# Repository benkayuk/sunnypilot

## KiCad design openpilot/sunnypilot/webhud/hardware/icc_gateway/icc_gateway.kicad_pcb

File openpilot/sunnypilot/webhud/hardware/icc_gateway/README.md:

# ICC CAN gateway board (Fisker Ocean, IBUS1 / IBUS2 man-in-the-middle)

KiCad 10 project. Sits between the car harness and the ICC (head unit) main connector J1
(Molex stAK50h 160013-0641), passes every circuit straight through except the two CAN buses,
which go through a Teensy 4.1 gateway with a normally-closed relay bypass.

## Files

| File | What |
|---|---|
| `icc_gateway.kicad_pro/.kicad_sch` | root sheet: five sub-sheets |
| `connectors.kicad_sch` | J1 (car harness header) and J2 (ICC-side solder field), 58 pass-through nets, CAN taps |
| `power.kicad_sch` | fuse, reverse/TVS protection, LMR36510 5 V buck, wake logic on EN |
| `can.kicad_sch` | 2x TJA1043 (car side, INH wake) + 2x TJA1051T/3 (ICC side), ESD, decoupling |
| `bypass.kicad_sch` | 4x G6S-2 relays (bridge + switched 120 R terminators), ULN2003A driver |
| `mcu.kicad_sch` | Teensy 4.1, MCP2518FD (SPI, 4th CAN), KL15 sense, LEDs, RTC cell |
| `lib/icc_gateway.kicad_sym` | stAK50h connector symbol (2 units: bay A / bay B), typed Teensy 4.1 symbol |
| `lib/icc_gateway.pretty/Molex_stAK50h_160013-0641.kicad_mod` | header footprint built from Molex SD-160013-0001 |
| `lib/icc_gateway.pretty/ICC_wire_pads_2x29.kicad_mod` | J2: 58 solder holes for the ICC pigtail (1.3 mm signal, 2.0 mm power/speaker), grouped like the header |
| `lib/teensy.pretty/Teensy41.kicad_mod` | Teensy 4.1 footprint (XenGi community library) |

Schematic edits were made through the Konnect MCP tools (`tools/konnect_mcp.py` is a stdio client for
it). `tools/design.py` holds the full component and net table, `tools/footprint_stak50h.py` generates
the header footprint, `tools/place_plan.py` the board placement.

## Connector facts (from the Molex sales drawing)

- 2 bays x 29 circuits. Per bay: circuits 1-8 are the 1.20 mm blades (two rows of four on
  4.00 mm pitch, d1.30 holes), circuits 9-29 are 0.50 mm terminals (three rows of seven on
  2.00 mm pitch, d1.10 holes). Rows are 3.00 mm apart at 13.30 / 16.30 / 19.30 / 22.30 / 25.30
  from the locator-peg row; circuits 23-29 are the row nearest the pegs, 1-4 the farthest.
- Locator pegs 2x d3.75 on 29.85 mm centers, 8.85 mm behind the mating-face edge. Bay pitch
  19.60 mm. Body 40.39 mm wide.
- **Pin-1 handedness must be verified on a sample header before ordering boards.** Molex's
  "PCB layout for reference" picture puts circuit 1 bottom-left with the face at the top. The
  section view shows the top face rows landing farthest from the face, and the front view has
  pin 1 top-left, which together put pin 1 on the *right* of a component-side view. The
  footprint therefore mirrors Molex's picture (`MIRROR = True` in `footprint_stak50h.py`).
  Check with a continuity test from the face to the tails on one header; if pin 1 is on the
  left when the face points away from you, set `MIRROR = False` and regenerate.

## Pin assignment (Teensy 4.1)

| Function | Teensy pin |
|---|---|
| CAN1 (car IBUS1, TJA1043 U2) | 22 TX / 23 RX |
| CAN2 (car IBUS2, TJA1043 U3) | 1 TX / 0 RX |
| CAN3 (ICC IBUS1, TJA1051T/3 U4) | 31 TX / 30 RX |
| SPI to MCP2518FD (ICC IBUS2, U5) | 11 MOSI, 12 MISO, 13 SCK, 10 CS, 9 INT |
| Relays RLY1..RLY4 (K1 bridge IBUS1, K2 bridge IBUS2, K3 terms IBUS1, K4 terms IBUS2) | 2, 3, 4, 5 |
| U2 STBN / EN / ERRN | 6 / 7 / 8 |
| U3 STBN / EN / ERRN | 14 / 15 / 16 |
| KL15 sense (100k/22k divider) | 17 (A3) |
| LEDs active / car / ICC | 24 / 25 / 26 |

The Teensy plugs into two 1x24 female 2.54 mm socket strips (add them to the order; they are not
in the schematic BOM). Only the two outer pin rows are used; the inboard VBAT pad cannot reach a
socket, so there is no RTC backup cell.

Cut the Teensy's VUSB-to-VIN pad before the first external power-up.

## ICC side

J2 is a solder field, not a second header. Make one pigtail: a 160014-0014 (bay A, key 4) and a
160014-0011 (bay B, key 1) receptacle with crimped leads, or a salvaged ICC harness stub, and solder the
58 wires into J2 (square pad = circuit 1 of each bay, bay B on the left, bay A on the right, circuits
1-8 on the large holes). This avoids a second header and a second set of 0.5 mm crimps.

## Power and wake

VBATT (J1-A1) -> 0.5 A polyfuse -> SS36 -> SMBJ33A clamp -> `VIN_PROT` -> LMR36510 (5 V, up to
65 V in) -> Teensy VIN. The regulator EN is pulled down and driven through BAT54 diodes from the
two TJA1043 INH outputs and from KL15 (10k), so the board is unpowered while the car sleeps and
wakes on either bus or on ignition. KL15 also feeds both TJA1043 WAKE pins through 10k.

## Relay bypass

De-energized (board off or dead): K1/K2 bridge car<->ICC on both buses and K3/K4 leave the
on-board 120 R terminators disconnected, so the ICC sits on the stock buses. Energized: the
bridges open, the gateway's four transceivers own the four segments, and the terminators
(car-side and ICC-side, both buses) are switched in. Populate R20/R22 (car-side terminators)
only if the measurement at the ICC connector shows the car bus lost its terminator when the
ICC was cut.

## Status (2026-10-07)

- Schematic complete, ERC clean (0/0). `icc_gateway_schematic.pdf`, `icc_gateway_bom.csv`.
- PCB routed and **DRC clean (0 errors)**: 110 x 100 mm, 4 layers (F.Cu signal, In1.Cu GND plane, In2.Cu
  signal, B.Cu signal), solid GND pours top and bottom, netclasses Power 1.0 mm / Audio 0.8 / CAN 0.3 /
  Default 0.15, min clearance 0.15, min track 0.09 (Freerouting neck-downs at pads), vias 0.6/0.3.
  Fab as a JLCPCB 4-layer board. Gerbers + drills: `gerbers/`, `icc_gateway_gerbers.zip`.
  Renders: `routing/icc_gateway_final_top.png`, `routing/icc_gateway_final_bottom.png`.
- Assembly: `assembly/icc_gateway-cpl.csv` (JLCPCB pick-and-place columns, KiCad coordinates, all 66 placed
  footprints on Top, rotations as placed) and `assembly/icc_gateway-bom-jlc.csv` (JLC columns; the LCSC
  part number column is empty and must be filled before ordering SMT assembly). The raw KiCad position
  file is `assembly/icc_gateway-positions.csv`. `assembly/icc_gateway-bom-mouser.csv` is the ordering BOM with
  manufacturer and Mouser part numbers (stock checked 2026-10-07); the MCP2518FD SOIC is backordered at
  Mouser, the MCP2517FD-H/SL is the in-stock drop-in.
- Remaining DRC warnings are cosmetic (silk overlaps, tiny Teensy silk text, the J1 silk box clipped
  at the board edge where the connector face overhangs, four mounting holes not in the schematic).
- Routing was done with Freerouting 2.5.0 (`tools/route_pipeline_r2.sh`: KiCad python DSN export, Freerouting,
  SES import) plus hand fixes in `tools/fixup*.py` and `tools/gnd_fixup.py`.

## Before ordering

1. Verify stAK50h pin-1 handedness on a sample header (see "Connector facts"); flip `MIRROR` and regenerate
   `Molex_stAK50h_160013-0641` + re-run the schematic sync if it is wrong.
2. Check J1's mating-face overhang against the enclosure: the face sits 8.85 mm in front of the pegs and
   the board edge is at the face plane.
3. Measure the car-side bus termination before populating R20/R22.

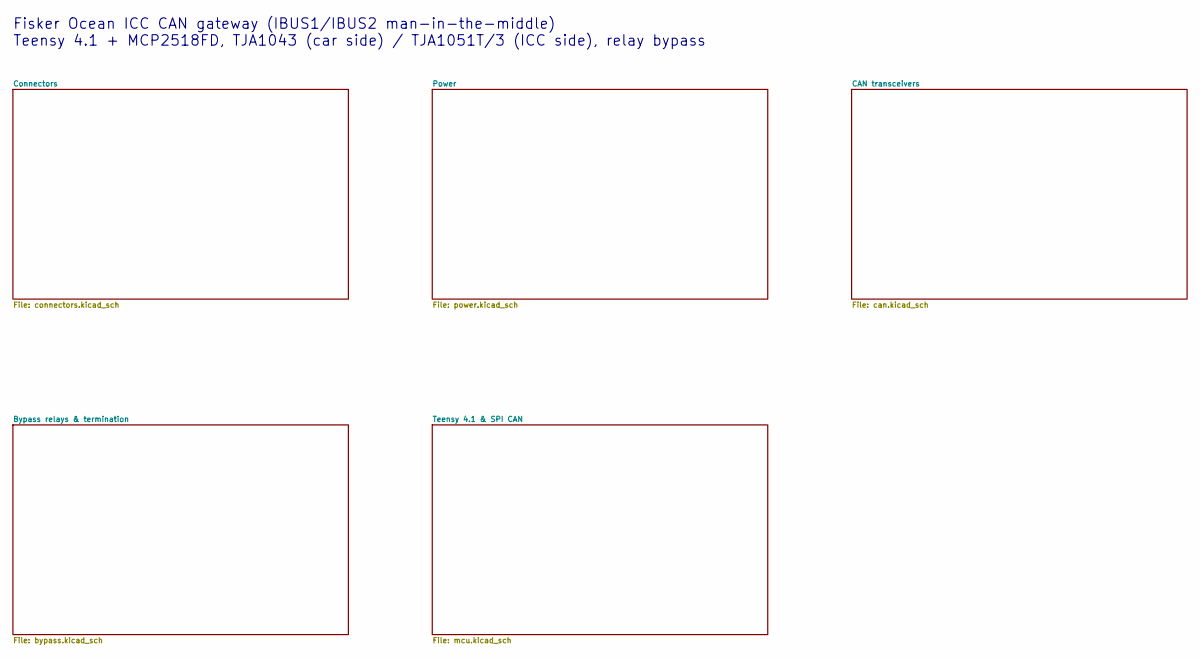
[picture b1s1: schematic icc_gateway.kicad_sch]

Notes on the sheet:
Fisker Ocean ICC CAN gateway (IBUS1/IBUS2 man-in-the-middle) Teensy 4.1 + MCP2518FD, TJA1043 (car side) / TJA1051T/3 (ICC side), relay bypass

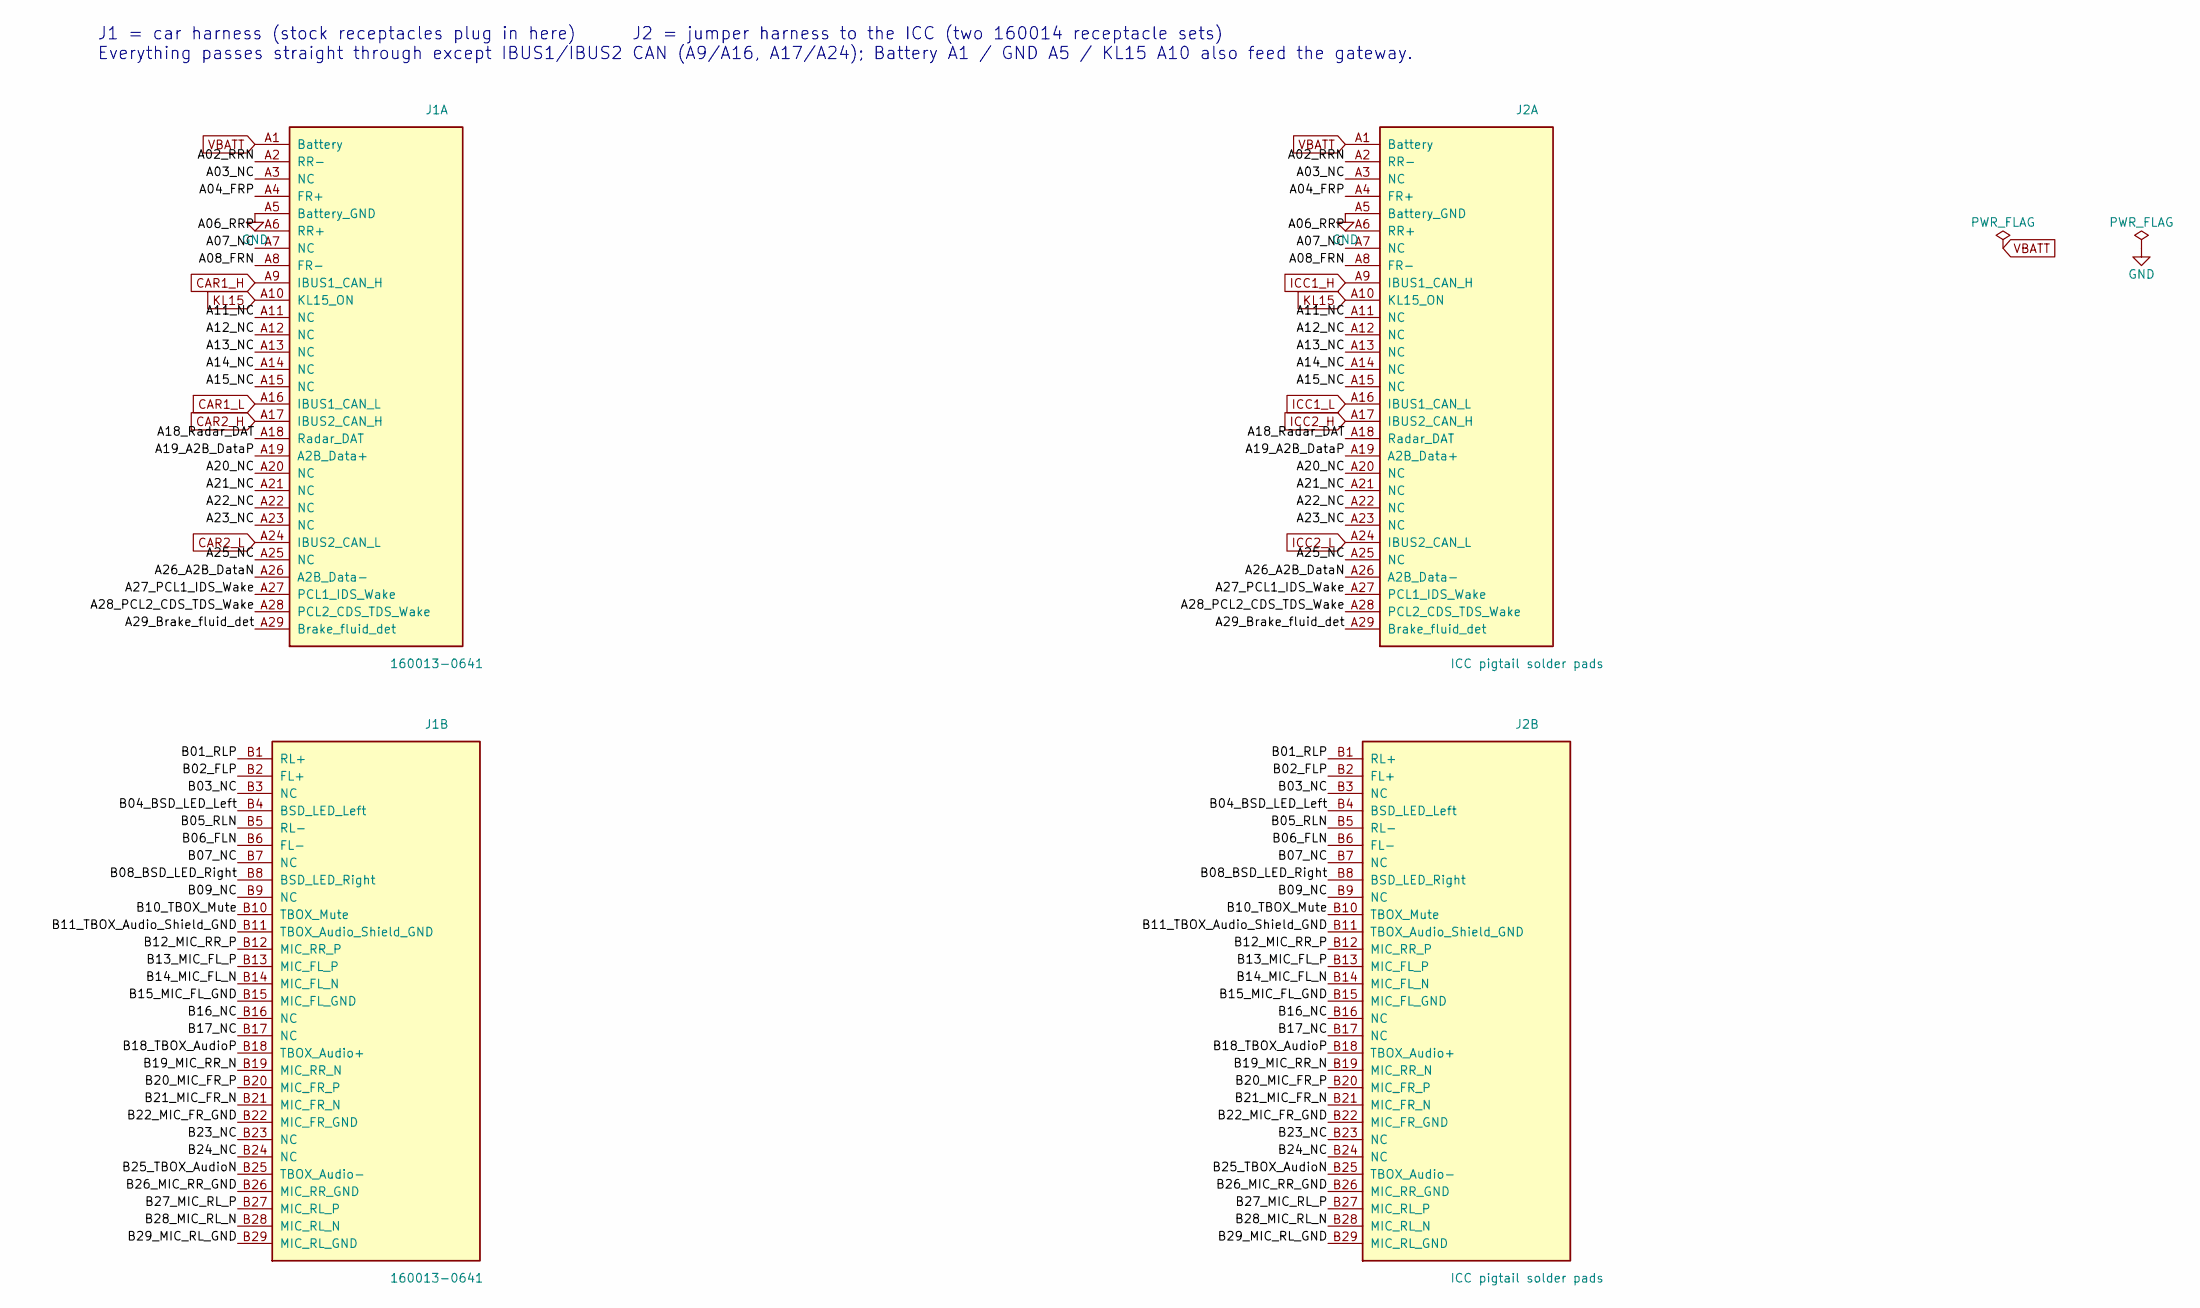
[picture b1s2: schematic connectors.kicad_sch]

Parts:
J1: 160013-0641; Molex_stAK50h_160013-0641
J2: ICC pigtail solder pads; ICC_wire_pads_2x29

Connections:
/Connectors/A02_RRN: J1.A2 (RR-), J2.A2 (RR-)
/Connectors/A03_NC: J1.A3 (NC), J2.A3 (NC)
/Connectors/A04_FRP: J1.A4 (FR+), J2.A4 (FR+)
/Connectors/A06_RRP: J1.A6 (RR+), J2.A6 (RR+)
/Connectors/A07_NC: J1.A7 (NC), J2.A7 (NC)
/Connectors/A08_FRN: J1.A8 (FR-), J2.A8 (FR-)
/Connectors/A11_NC: J1.A11 (NC), J2.A11 (NC)
/Connectors/A12_NC: J1.A12 (NC), J2.A12 (NC)
/Connectors/A13_NC: J1.A13 (NC), J2.A13 (NC)
/Connectors/A14_NC: J1.A14 (NC), J2.A14 (NC)
/Connectors/A15_NC: J1.A15 (NC), J2.A15 (NC)
/Connectors/A18_Radar_DAT: J1.A18 (Radar_DAT), J2.A18 (Radar_DAT)
/Connectors/A19_A2B_DataP: J1.A19 (A2B_Data+), J2.A19 (A2B_Data+)
/Connectors/A20_NC: J1.A20 (NC), J2.A20 (NC)
/Connectors/A21_NC: J1.A21 (NC), J2.A21 (NC)
/Connectors/A22_NC: J1.A22 (NC), J2.A22 (NC)
/Connectors/A23_NC: J1.A23 (NC), J2.A23 (NC)
/Connectors/A25_NC: J1.A25 (NC), J2.A25 (NC)
/Connectors/A26_A2B_DataN: J1.A26 (A2B_Data-), J2.A26 (A2B_Data-)
/Connectors/A27_PCL1_IDS_Wake: J1.A27 (PCL1_IDS_Wake), J2.A27 (PCL1_IDS_Wake)
/Connectors/A28_PCL2_CDS_TDS_Wake: J1.A28 (PCL2_CDS_TDS_Wake), J2.A28 (PCL2_CDS_TDS_Wake)
/Connectors/A29_Brake_fluid_det: J1.A29 (Brake_fluid_det), J2.A29 (Brake_fluid_det)
/Connectors/B01_RLP: J1.B1 (RL+), J2.B1 (RL+)
/Connectors/B02_FLP: J1.B2 (FL+), J2.B2 (FL+)
/Connectors/B03_NC: J1.B3 (NC), J2.B3 (NC)
/Connectors/B04_BSD_LED_Left: J1.B4 (BSD_LED_Left), J2.B4 (BSD_LED_Left)
/Connectors/B05_RLN: J1.B5 (RL-), J2.B5 (RL-)
/Connectors/B06_FLN: J1.B6 (FL-), J2.B6 (FL-)
/Connectors/B07_NC: J1.B7 (NC), J2.B7 (NC)
/Connectors/B08_BSD_LED_Right: J1.B8 (BSD_LED_Right), J2.B8 (BSD_LED_Right)
/Connectors/B09_NC: J1.B9 (NC), J2.B9 (NC)
/Connectors/B10_TBOX_Mute: J1.B10 (TBOX_Mute), J2.B10 (TBOX_Mute)
/Connectors/B11_TBOX_Audio_Shield_GND: J1.B11 (TBOX_Audio_Shield_GND), J2.B11 (TBOX_Audio_Shield_GND)
/Connectors/B12_MIC_RR_P: J1.B12 (MIC_RR_P), J2.B12 (MIC_RR_P)
/Connectors/B13_MIC_FL_P: J1.B13 (MIC_FL_P), J2.B13 (MIC_FL_P)
/Connectors/B14_MIC_FL_N: J1.B14 (MIC_FL_N), J2.B14 (MIC_FL_N)
/Connectors/B15_MIC_FL_GND: J1.B15 (MIC_FL_GND), J2.B15 (MIC_FL_GND)
/Connectors/B16_NC: J1.B16 (NC), J2.B16 (NC)
/Connectors/B17_NC: J1.B17 (NC), J2.B17 (NC)
/Connectors/B18_TBOX_AudioP: J1.B18 (TBOX_Audio+), J2.B18 (TBOX_Audio+)
/Connectors/B19_MIC_RR_N: J1.B19 (MIC_RR_N), J2.B19 (MIC_RR_N)
/Connectors/B20_MIC_FR_P: J1.B20 (MIC_FR_P), J2.B20 (MIC_FR_P)
/Connectors/B21_MIC_FR_N: J1.B21 (MIC_FR_N), J2.B21 (MIC_FR_N)
/Connectors/B22_MIC_FR_GND: J1.B22 (MIC_FR_GND), J2.B22 (MIC_FR_GND)
/Connectors/B23_NC: J1.B23 (NC), J2.B23 (NC)
/Connectors/B24_NC: J1.B24 (NC), J2.B24 (NC)
/Connectors/B25_TBOX_AudioN: J1.B25 (TBOX_Audio-), J2.B25 (TBOX_Audio-)
/Connectors/B26_MIC_RR_GND: J1.B26 (MIC_RR_GND), J2.B26 (MIC_RR_GND)
/Connectors/B27_MIC_RL_P: J1.B27 (MIC_RL_P), J2.B27 (MIC_RL_P)
/Connectors/B28_MIC_RL_N: J1.B28 (MIC_RL_N), J2.B28 (MIC_RL_N)
/Connectors/B29_MIC_RL_GND: J1.B29 (MIC_RL_GND), J2.B29 (MIC_RL_GND)
CAR1_H: J1.A9 (IBUS1_CAN_H); also elsewhere on the board
CAR1_L: J1.A16 (IBUS1_CAN_L); also elsewhere on the board
CAR2_H: J1.A17 (IBUS2_CAN_H); also elsewhere on the board
CAR2_L: J1.A24 (IBUS2_CAN_L); also elsewhere on the board
GND: J1.A5 (Battery_GND), J2.A5 (Battery_GND); also elsewhere on the board
ICC1_H: J2.A9 (IBUS1_CAN_H); also elsewhere on the board
ICC1_L: J2.A16 (IBUS1_CAN_L); also elsewhere on the board
ICC2_H: J2.A17 (IBUS2_CAN_H); also elsewhere on the board
ICC2_L: J2.A24 (IBUS2_CAN_L); also elsewhere on the board
KL15: J1.A10 (KL15_ON), J2.A10 (KL15_ON); also elsewhere on the board
VBATT: J1.A1 (Battery), J2.A1 (Battery); also elsewhere on the board

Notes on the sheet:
J1 = car harness (stock receptacles plug in here) J2 = jumper harness to the ICC (two 160014 receptacle sets) Everything passes straight through except IBUS1/IBUS2 CAN (A9/A16, A17/A24); Battery A1 / GND A5 / KL15 A10 also feed the gateway.

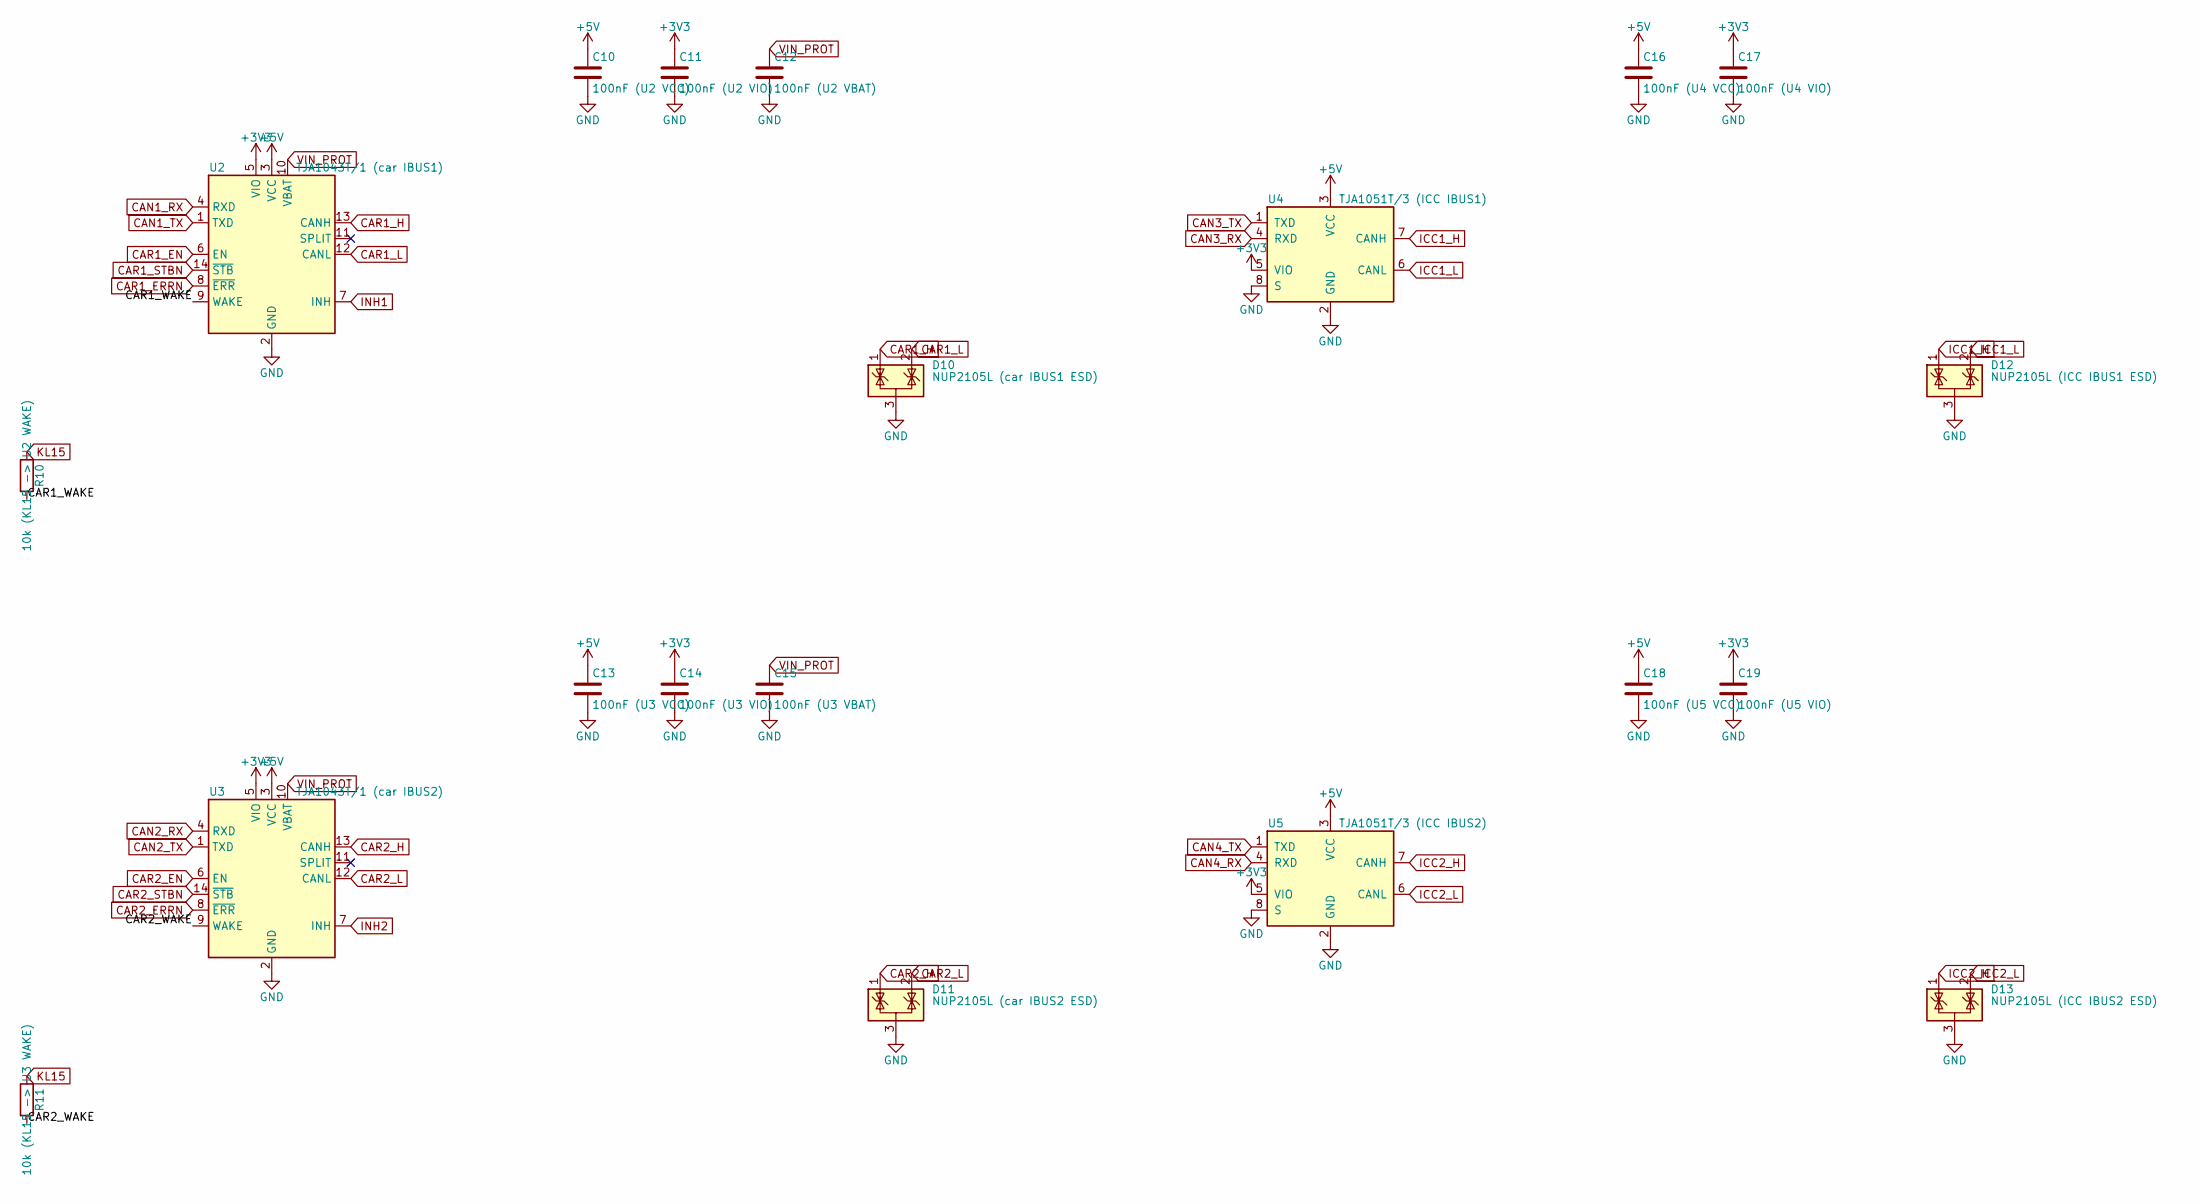
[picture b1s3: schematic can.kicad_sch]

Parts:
C10: 100nF (U2 VCC); C_0805_2012Metric
C11: 100nF (U2 VIO); C_0805_2012Metric
C12: 100nF (U2 VBAT); C_0805_2012Metric
C13: 100nF (U3 VCC); C_0805_2012Metric
C14: 100nF (U3 VIO); C_0805_2012Metric
C15: 100nF (U3 VBAT); C_0805_2012Metric
C16: 100nF (U4 VCC); C_0805_2012Metric
C17: 100nF (U4 VIO); C_0805_2012Metric
C18: 100nF (U5 VCC); C_0805_2012Metric
C19: 100nF (U5 VIO); C_0805_2012Metric
D10: NUP2105L (car IBUS1 ESD); SOT-23-3
D11: NUP2105L (car IBUS2 ESD); SOT-23-3
D12: NUP2105L (ICC IBUS1 ESD); SOT-23-3
D13: NUP2105L (ICC IBUS2 ESD); SOT-23-3
R10: 10k (KL15 -> U2 WAKE); R_0805_2012Metric
R11: 10k (KL15 -> U3 WAKE); R_0805_2012Metric
U2: TJA1043T/1 (car IBUS1); SOIC-14_3.9x8.7mm_P1.27mm
U3: TJA1043T/1 (car IBUS2); SOIC-14_3.9x8.7mm_P1.27mm
U4: TJA1051T/3 (ICC IBUS1); SOIC-8_3.9x4.9mm_P1.27mm
U5: TJA1051T/3 (ICC IBUS2); SOIC-8_3.9x4.9mm_P1.27mm

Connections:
+3V3: C11.1, C14.1, C17.1, C19.1, U2.5 (VIO), U3.5 (VIO), U4.5 (VIO), U5.5 (VIO); also elsewhere on the board
+5V: C10.1, C13.1, C16.1, C18.1, U2.3 (VCC), U3.3 (VCC), U4.3 (VCC), U5.3 (VCC); also elsewhere on the board
/CAN transceivers/CAR1_WAKE: R10.2, U2.9 (WAKE)
/CAN transceivers/CAR2_WAKE: R11.2, U3.9 (WAKE)
CAN1_RX: U2.4 (RXD); also elsewhere on the board
CAN1_TX: U2.1 (TXD); also elsewhere on the board
CAN2_RX: U3.4 (RXD); also elsewhere on the board
CAN2_TX: U3.1 (TXD); also elsewhere on the board
CAN3_RX: U4.4 (RXD); also elsewhere on the board
CAN3_TX: U4.1 (TXD); also elsewhere on the board
CAN4_RX: U5.4 (RXD); also elsewhere on the board
CAN4_TX: U5.1 (TXD); also elsewhere on the board
CAR1_EN: U2.6 (EN); also elsewhere on the board
CAR1_ERRN: U2.8 (~ERR); also elsewhere on the board
CAR1_H: D10.1 (K), U2.13 (CANH); also elsewhere on the board
CAR1_L: D10.2 (K), U2.12 (CANL); also elsewhere on the board
CAR1_STBN: U2.14 (~STB); also elsewhere on the board
CAR2_EN: U3.6 (EN); also elsewhere on the board
CAR2_ERRN: U3.8 (~ERR); also elsewhere on the board
CAR2_H: D11.1 (K), U3.13 (CANH); also elsewhere on the board
CAR2_L: D11.2 (K), U3.12 (CANL); also elsewhere on the board
CAR2_STBN: U3.14 (~STB); also elsewhere on the board
GND: C10.2, C11.2, C12.2, C13.2, C14.2, C15.2, C16.2, C17.2, C18.2, C19.2, D10.3 (A), D11.3 (A), D12.3 (A), D13.3 (A), U2.2 (GND), U3.2 (GND), U4.2 (GND), U4.8 (S), U5.2 (GND), U5.8 (S); also elsewhere on the board
ICC1_H: D12.1 (K), U4.7 (CANH); also elsewhere on the board
ICC1_L: D12.2 (K), U4.6 (CANL); also elsewhere on the board
ICC2_H: D13.1 (K), U5.7 (CANH); also elsewhere on the board
ICC2_L: D13.2 (K), U5.6 (CANL); also elsewhere on the board
INH1: U2.7 (INH); also elsewhere on the board
INH2: U3.7 (INH); also elsewhere on the board
KL15: R10.1, R11.1; also elsewhere on the board
VIN_PROT: C12.1, C15.1, U2.10 (VBAT), U3.10 (VBAT); also elsewhere on the board

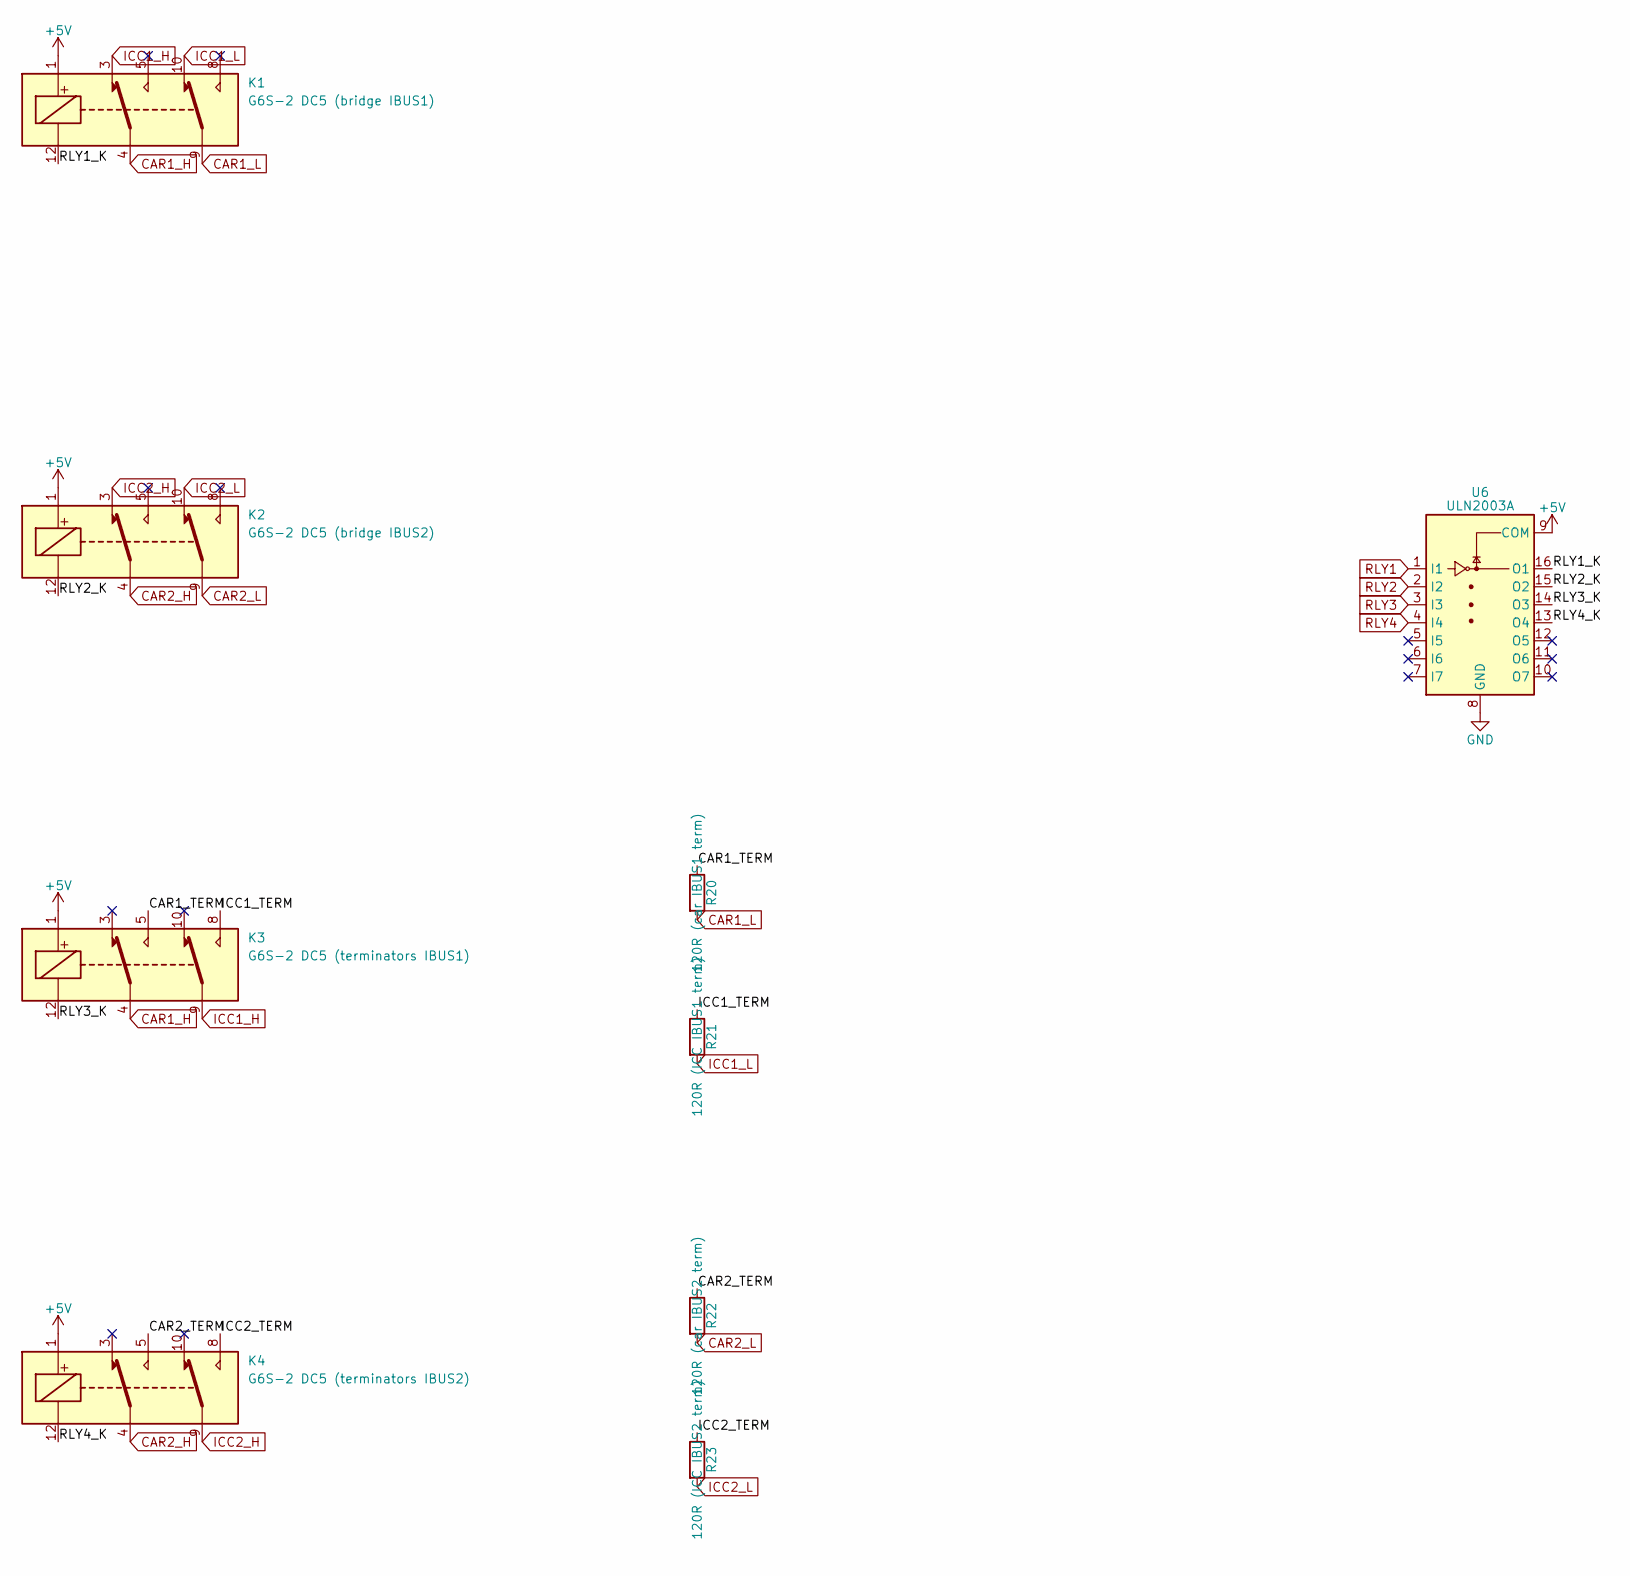
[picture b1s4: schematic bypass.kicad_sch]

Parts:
K1: G6S-2 DC5 (bridge IBUS1); Relay_DPDT_Omron_G6S-2
K2: G6S-2 DC5 (bridge IBUS2); Relay_DPDT_Omron_G6S-2
K3: G6S-2 DC5 (terminators IBUS1); Relay_DPDT_Omron_G6S-2
K4: G6S-2 DC5 (terminators IBUS2); Relay_DPDT_Omron_G6S-2
R20: 120R (car IBUS1 term); R_0805_2012Metric
R21: 120R (ICC IBUS1 term); R_0805_2012Metric
R22: 120R (car IBUS2 term); R_0805_2012Metric
R23: 120R (ICC IBUS2 term); R_0805_2012Metric
U6: ULN2003A; SOIC-16_3.9x9.9mm_P1.27mm

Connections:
+5V: K1.1, K2.1, K3.1, K4.1, U6.9 (COM); also elsewhere on the board
/Bypass relays & termination/CAR1_TERM: K3.5, R20.1
/Bypass relays & termination/CAR2_TERM: K4.5, R22.1
/Bypass relays & termination/ICC1_TERM: K3.8, R21.1
/Bypass relays & termination/ICC2_TERM: K4.8, R23.1
/Bypass relays & termination/RLY1_K: K1.12, U6.16 (O1)
/Bypass relays & termination/RLY2_K: K2.12, U6.15 (O2)
/Bypass relays & termination/RLY3_K: K3.12, U6.14 (O3)
/Bypass relays & termination/RLY4_K: K4.12, U6.13 (O4)
CAR1_H: K1.4, K3.4; also elsewhere on the board
CAR1_L: K1.9, R20.2; also elsewhere on the board
CAR2_H: K2.4, K4.4; also elsewhere on the board
CAR2_L: K2.9, R22.2; also elsewhere on the board
GND: U6.8 (GND); also elsewhere on the board
ICC1_H: K1.3, K3.9; also elsewhere on the board
ICC1_L: K1.10, R21.2; also elsewhere on the board
ICC2_H: K2.3, K4.9; also elsewhere on the board
ICC2_L: K2.10, R23.2; also elsewhere on the board
RLY1: U6.1 (I1); also elsewhere on the board
RLY2: U6.2 (I2); also elsewhere on the board
RLY3: U6.3 (I3); also elsewhere on the board
RLY4: U6.4 (I4); also elsewhere on the board

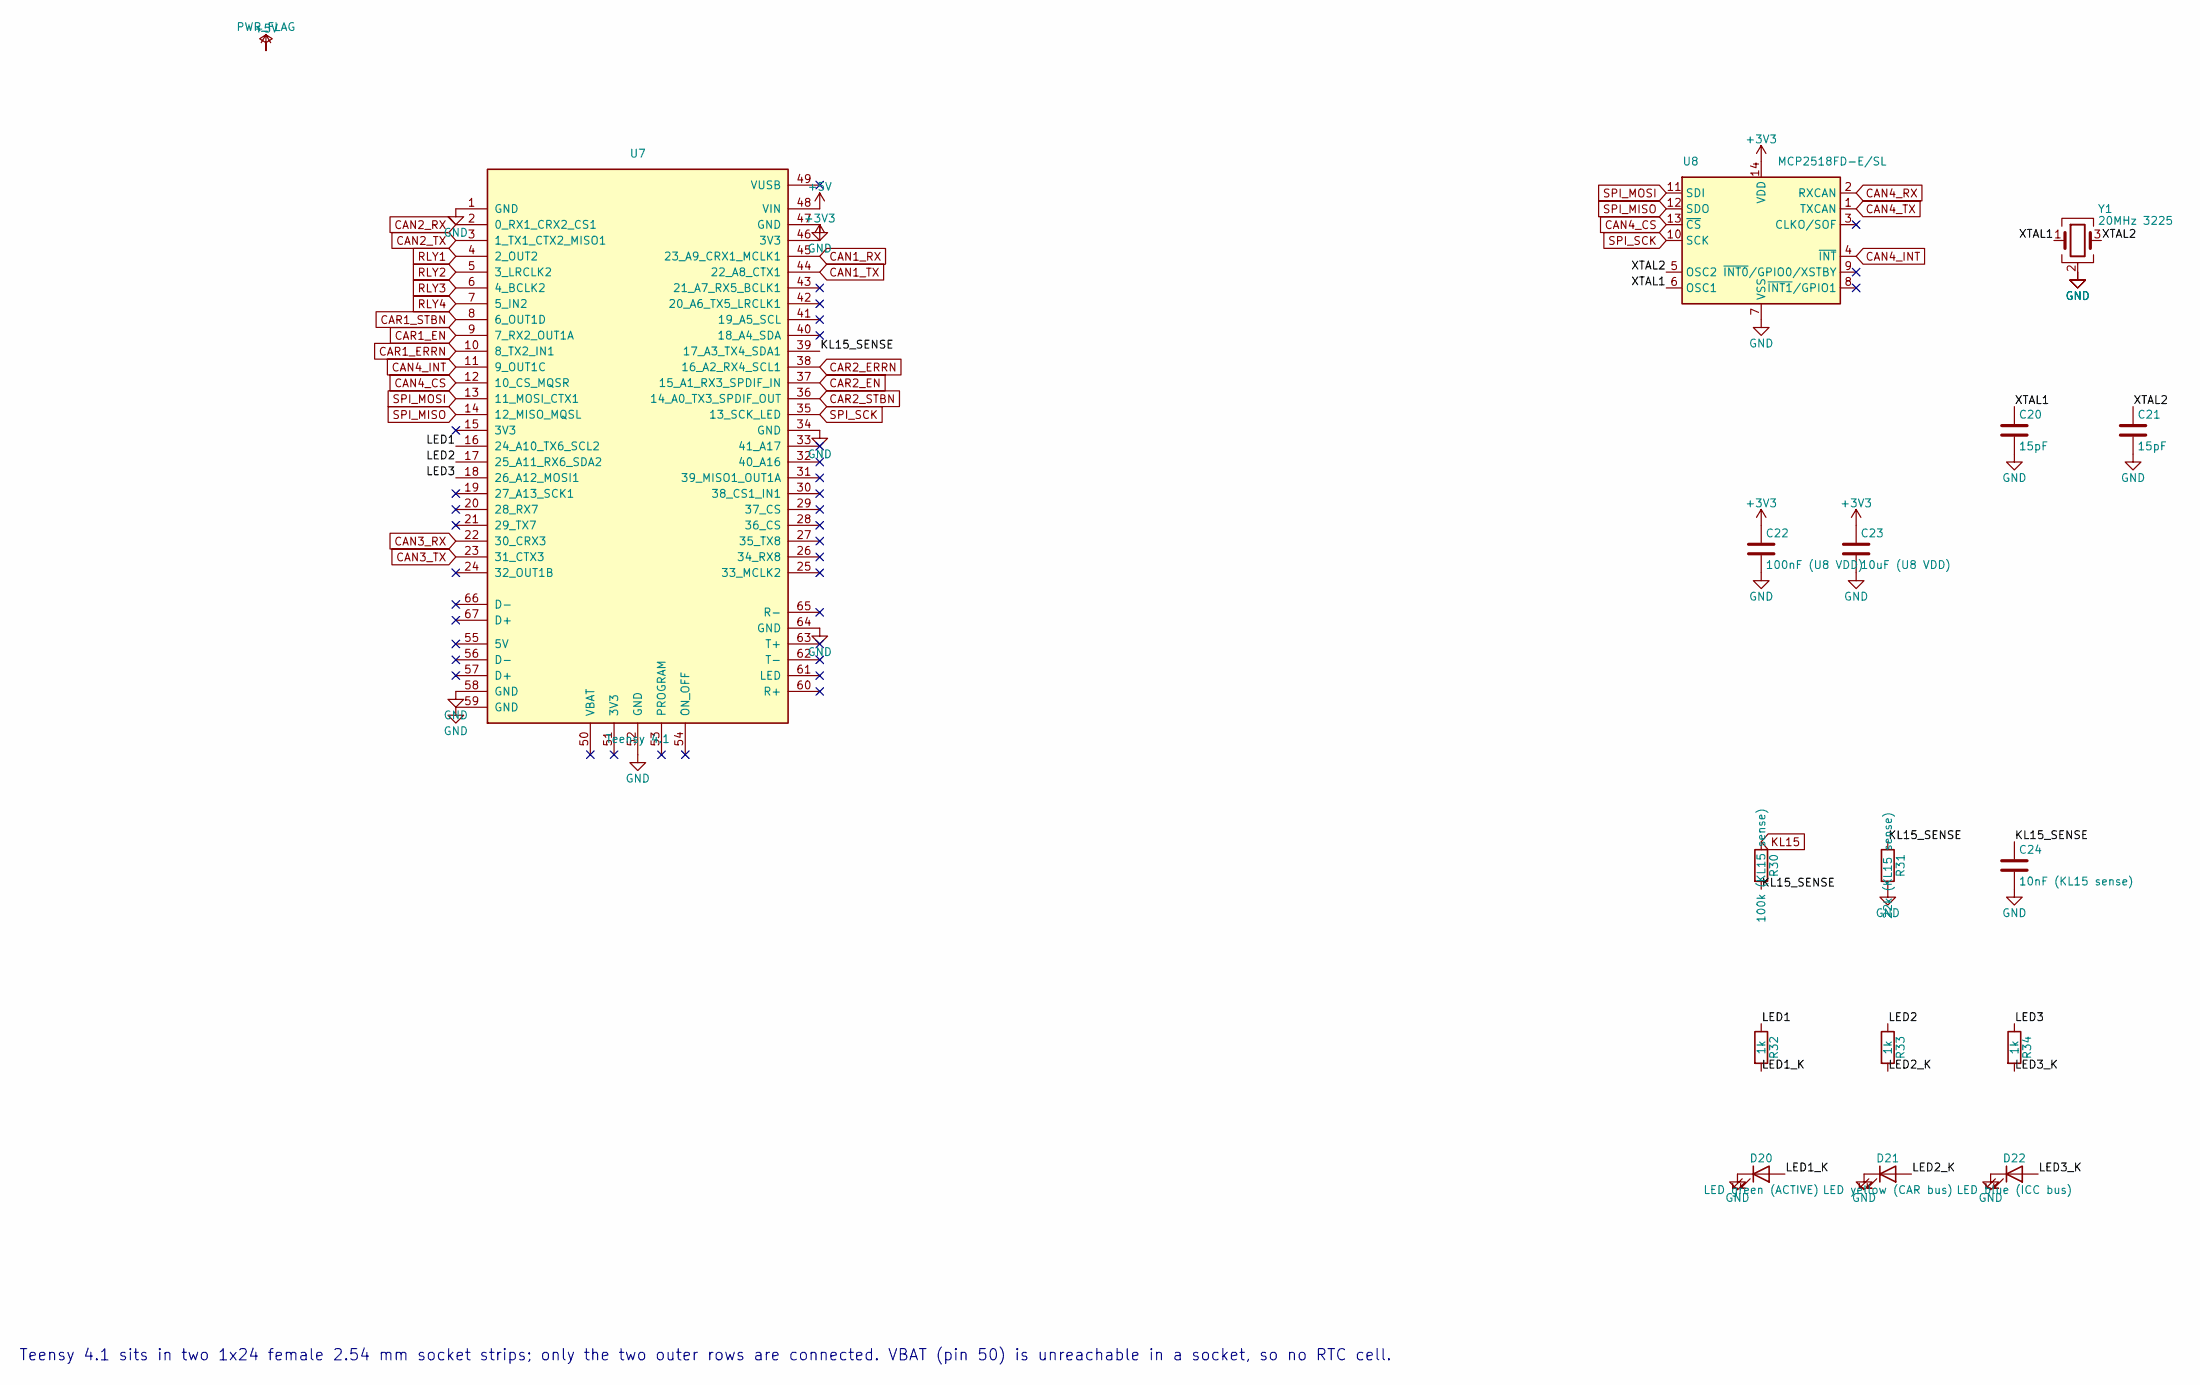
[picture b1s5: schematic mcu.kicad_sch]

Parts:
C20, C21: 15pF; C_0603_1608Metric
C22: 100nF (U8 VDD); C_0603_1608Metric
C23: 10uF (U8 VDD); C_0805_2012Metric
C24: 10nF (KL15 sense); C_0603_1608Metric
D20: LED green (ACTIVE); LED_0805_2012Metric
D21: LED yellow (CAR bus); LED_0805_2012Metric
D22: LED blue (ICC bus); LED_0805_2012Metric
R30: 100k (KL15 sense); R_0805_2012Metric
R31: 22k (KL15 sense); R_0805_2012Metric
R32, R33, R34: 1k; R_0805_2012Metric
U7: Teensy 4.1; Teensy41
U8: MCP2518FD-E/SL; SOIC-14_3.9x8.7mm_P1.27mm
Y1: 20MHz 3225; Crystal_SMD_3225-4Pin_3.2x2.5mm

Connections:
+3V3: C22.1, C23.1, U7.46 (3V3), U8.14 (VDD); also elsewhere on the board
+5V: U7.48 (VIN); also elsewhere on the board
/Teensy 4.1 & SPI CAN/KL15_SENSE: C24.1, R30.2, R31.1, U7.39 (17_A3_TX4_SDA1)
/Teensy 4.1 & SPI CAN/LED1: R32.1, U7.16 (24_A10_TX6_SCL2)
/Teensy 4.1 & SPI CAN/LED1_K: D20.2 (A), R32.2
/Teensy 4.1 & SPI CAN/LED2: R33.1, U7.17 (25_A11_RX6_SDA2)
/Teensy 4.1 & SPI CAN/LED2_K: D21.2 (A), R33.2
/Teensy 4.1 & SPI CAN/LED3: R34.1, U7.18 (26_A12_MOSI1)
/Teensy 4.1 & SPI CAN/LED3_K: D22.2 (A), R34.2
/Teensy 4.1 & SPI CAN/XTAL1: C20.1, U8.6 (OSC1), Y1.1
/Teensy 4.1 & SPI CAN/XTAL2: C21.1, U8.5 (OSC2), Y1.3
CAN1_RX: U7.45 (23_A9_CRX1_MCLK1); also elsewhere on the board
CAN1_TX: U7.44 (22_A8_CTX1); also elsewhere on the board
CAN2_RX: U7.2 (0_RX1_CRX2_CS1); also elsewhere on the board
CAN2_TX: U7.3 (1_TX1_CTX2_MISO1); also elsewhere on the board
CAN3_RX: U7.22 (30_CRX3); also elsewhere on the board
CAN3_TX: U7.23 (31_CTX3); also elsewhere on the board
CAN4_CS: U7.12 (10_CS_MQSR), U8.13 (~CS)
CAN4_INT: U7.11 (9_OUT1C), U8.4 (~INT)
CAN4_RX: U8.2 (RXCAN); also elsewhere on the board
CAN4_TX: U8.1 (TXCAN); also elsewhere on the board
CAR1_EN: U7.9 (7_RX2_OUT1A); also elsewhere on the board
CAR1_ERRN: U7.10 (8_TX2_IN1); also elsewhere on the board
CAR1_STBN: U7.8 (6_OUT1D); also elsewhere on the board
CAR2_EN: U7.37 (15_A1_RX3_SPDIF_IN); also elsewhere on the board
CAR2_ERRN: U7.38 (16_A2_RX4_SCL1); also elsewhere on the board
CAR2_STBN: U7.36 (14_A0_TX3_SPDIF_OUT); also elsewhere on the board
GND: C20.2, C21.2, C22.2, C23.2, C24.2, D20.1 (K), D21.1 (K), D22.1 (K), R31.2, U7.1 (GND), U7.34 (GND), U7.47 (GND), U7.52 (GND), U7.58 (GND), U7.59 (GND), U7.64 (GND), U8.7 (VSS), Y1.2 (G), Y1.4 (G); also elsewhere on the board
KL15: R30.1; also elsewhere on the board
RLY1: U7.4 (2_OUT2); also elsewhere on the board
RLY2: U7.5 (3_LRCLK2); also elsewhere on the board
RLY3: U7.6 (4_BCLK2); also elsewhere on the board
RLY4: U7.7 (5_IN2); also elsewhere on the board
SPI_MISO: U7.14 (12_MISO_MQSL), U8.12 (SDO)
SPI_MOSI: U7.13 (11_MOSI_CTX1), U8.11 (SDI)
SPI_SCK: U7.35 (13_SCK_LED), U8.10 (SCK)

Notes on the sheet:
Teensy 4.1 sits in two 1x24 female 2.54 mm socket strips; only the two outer rows are connected. VBAT (pin 50) is unreachable in a socket, so no RTC cell.
